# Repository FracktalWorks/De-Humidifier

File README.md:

# De-Humidifier

This is just a temporary file.

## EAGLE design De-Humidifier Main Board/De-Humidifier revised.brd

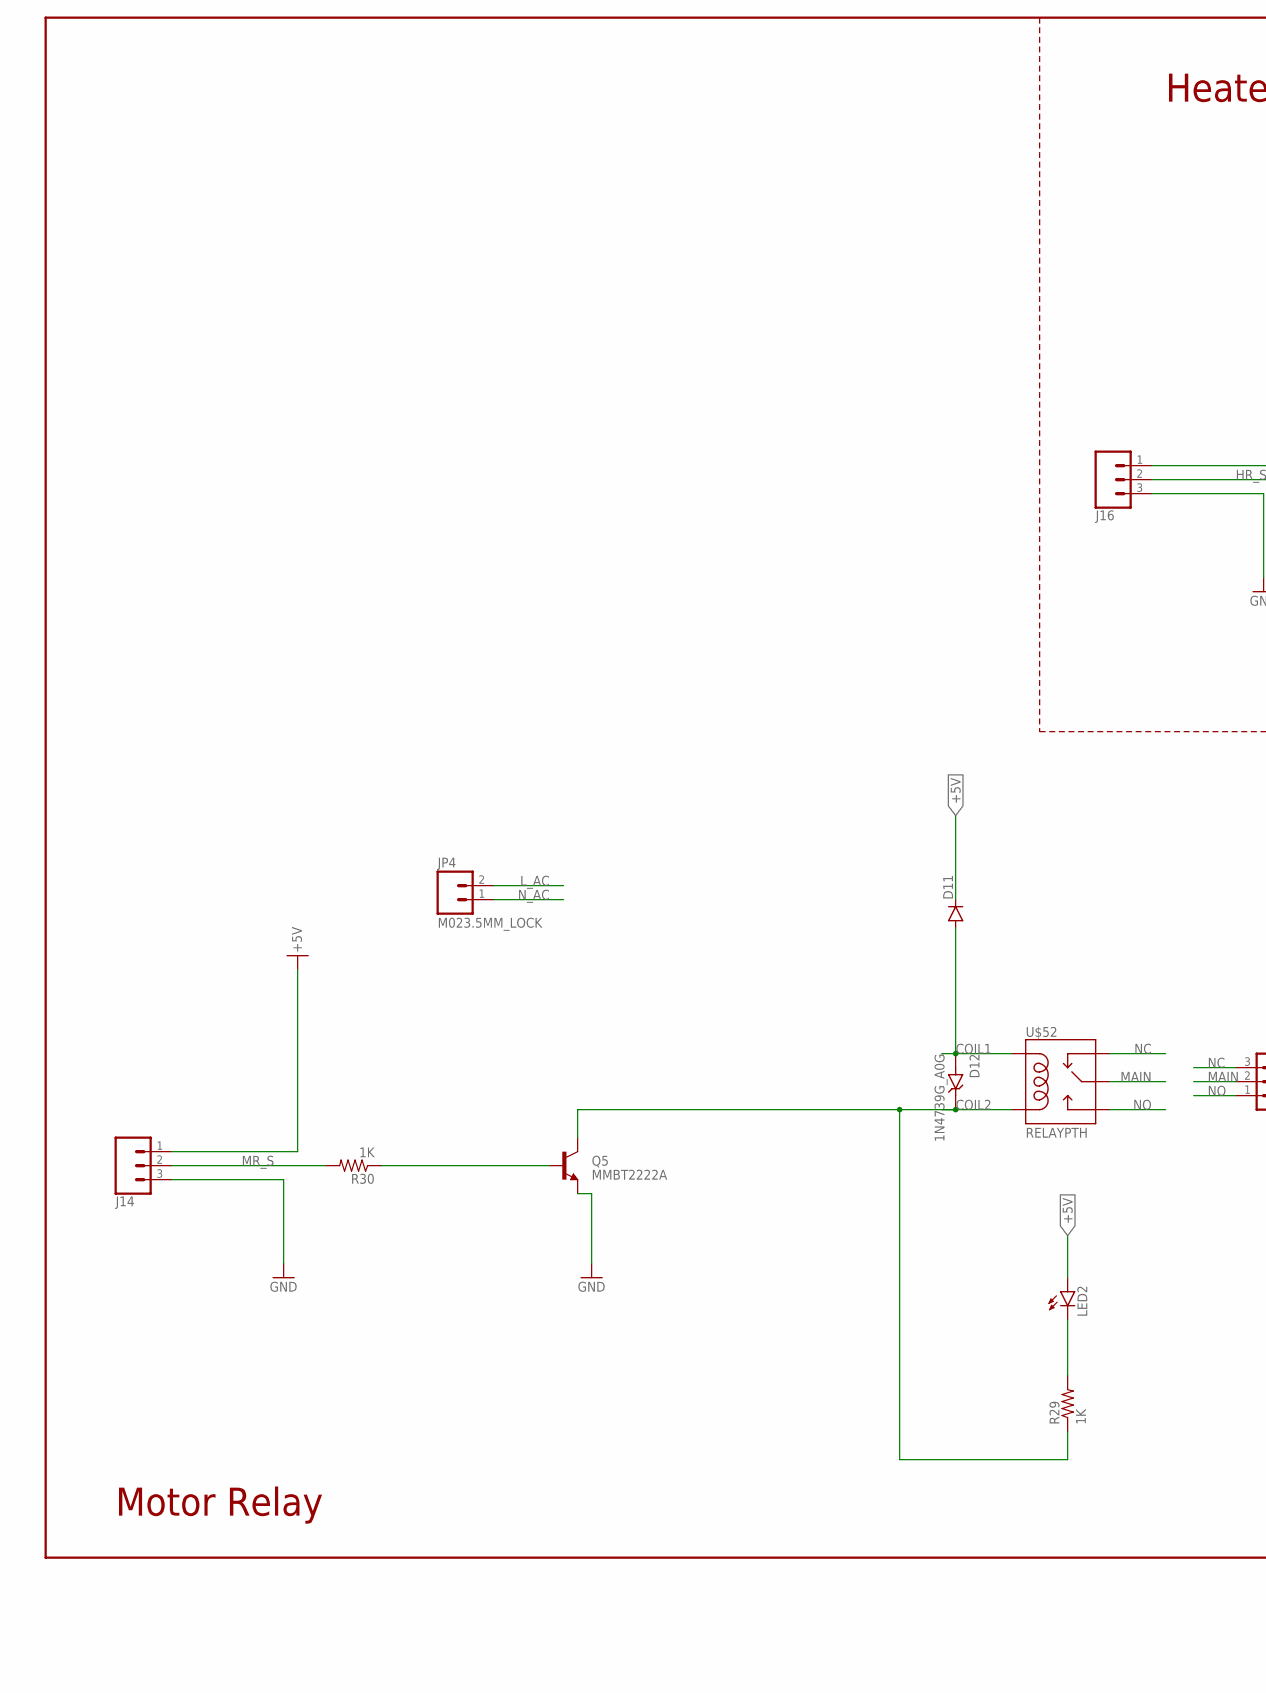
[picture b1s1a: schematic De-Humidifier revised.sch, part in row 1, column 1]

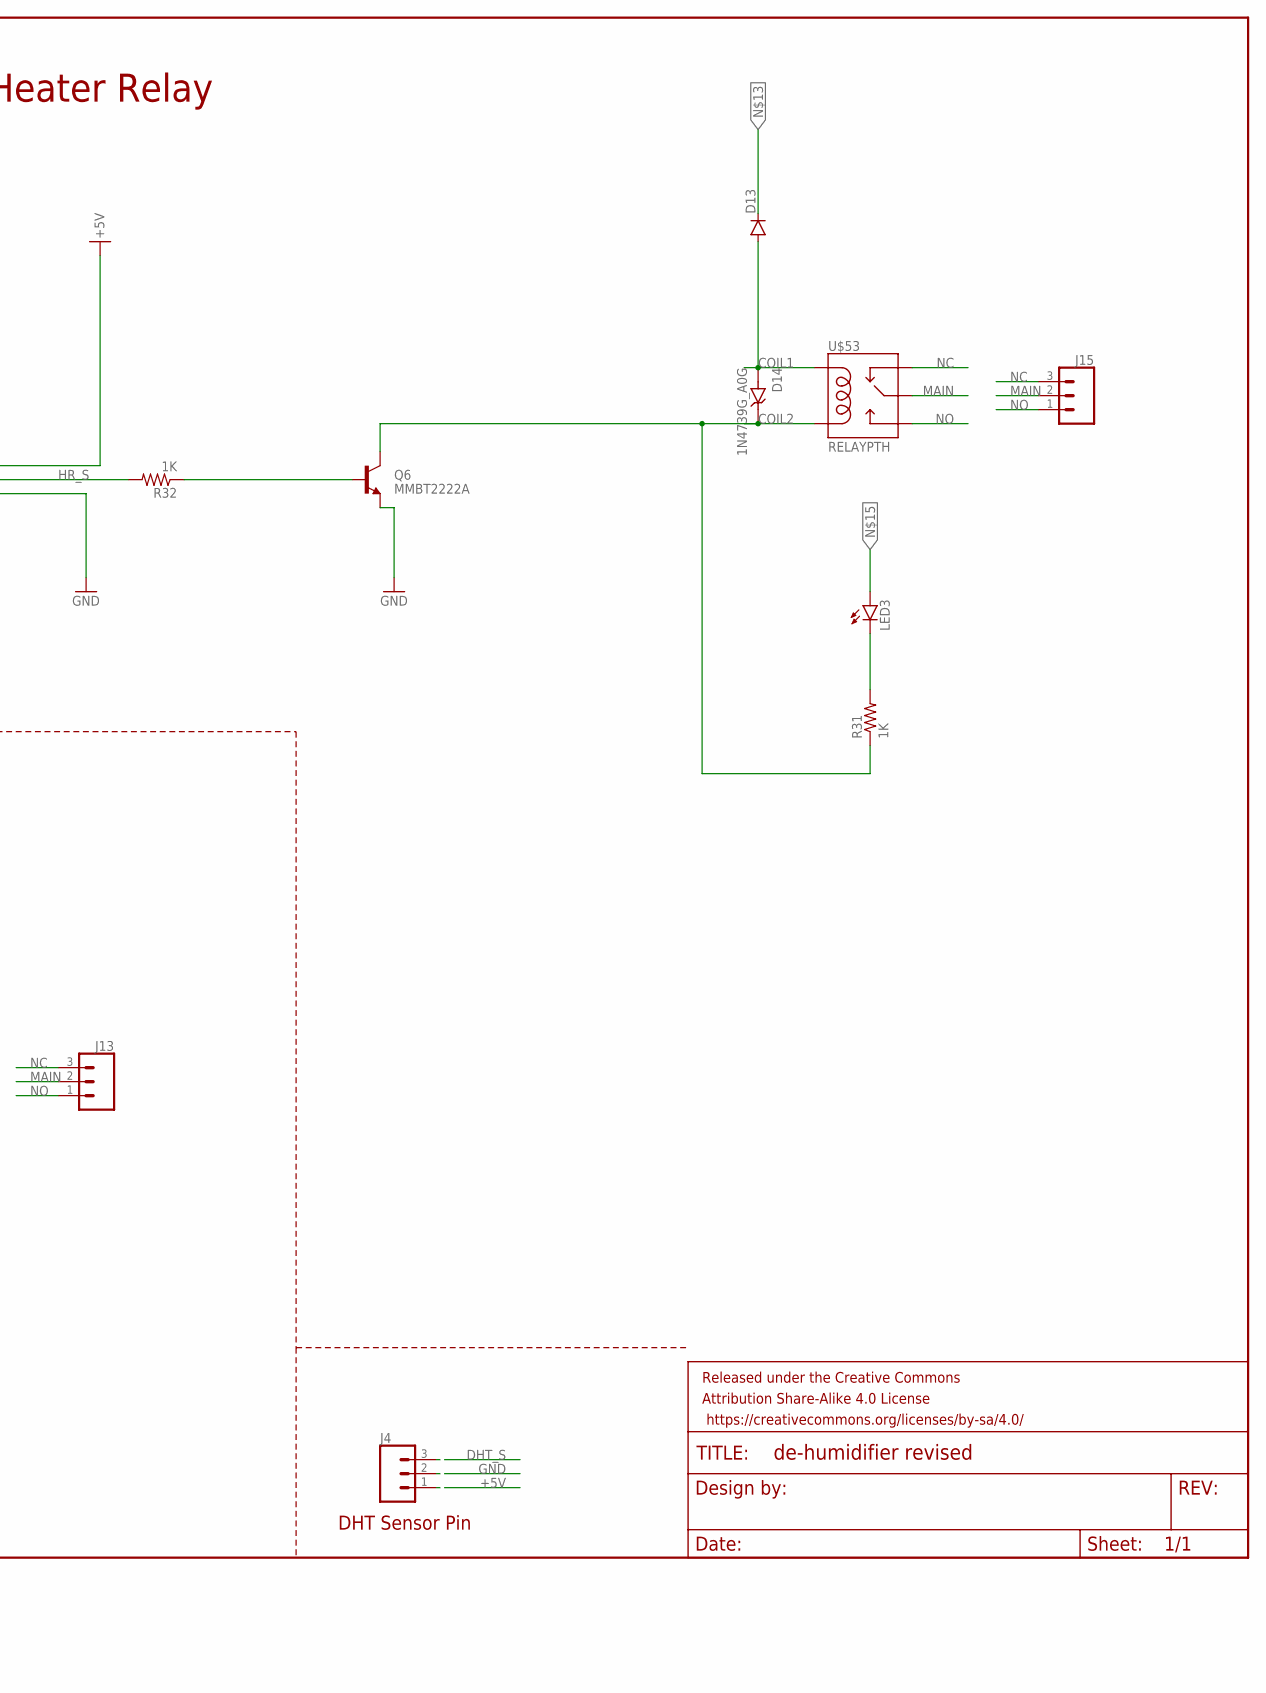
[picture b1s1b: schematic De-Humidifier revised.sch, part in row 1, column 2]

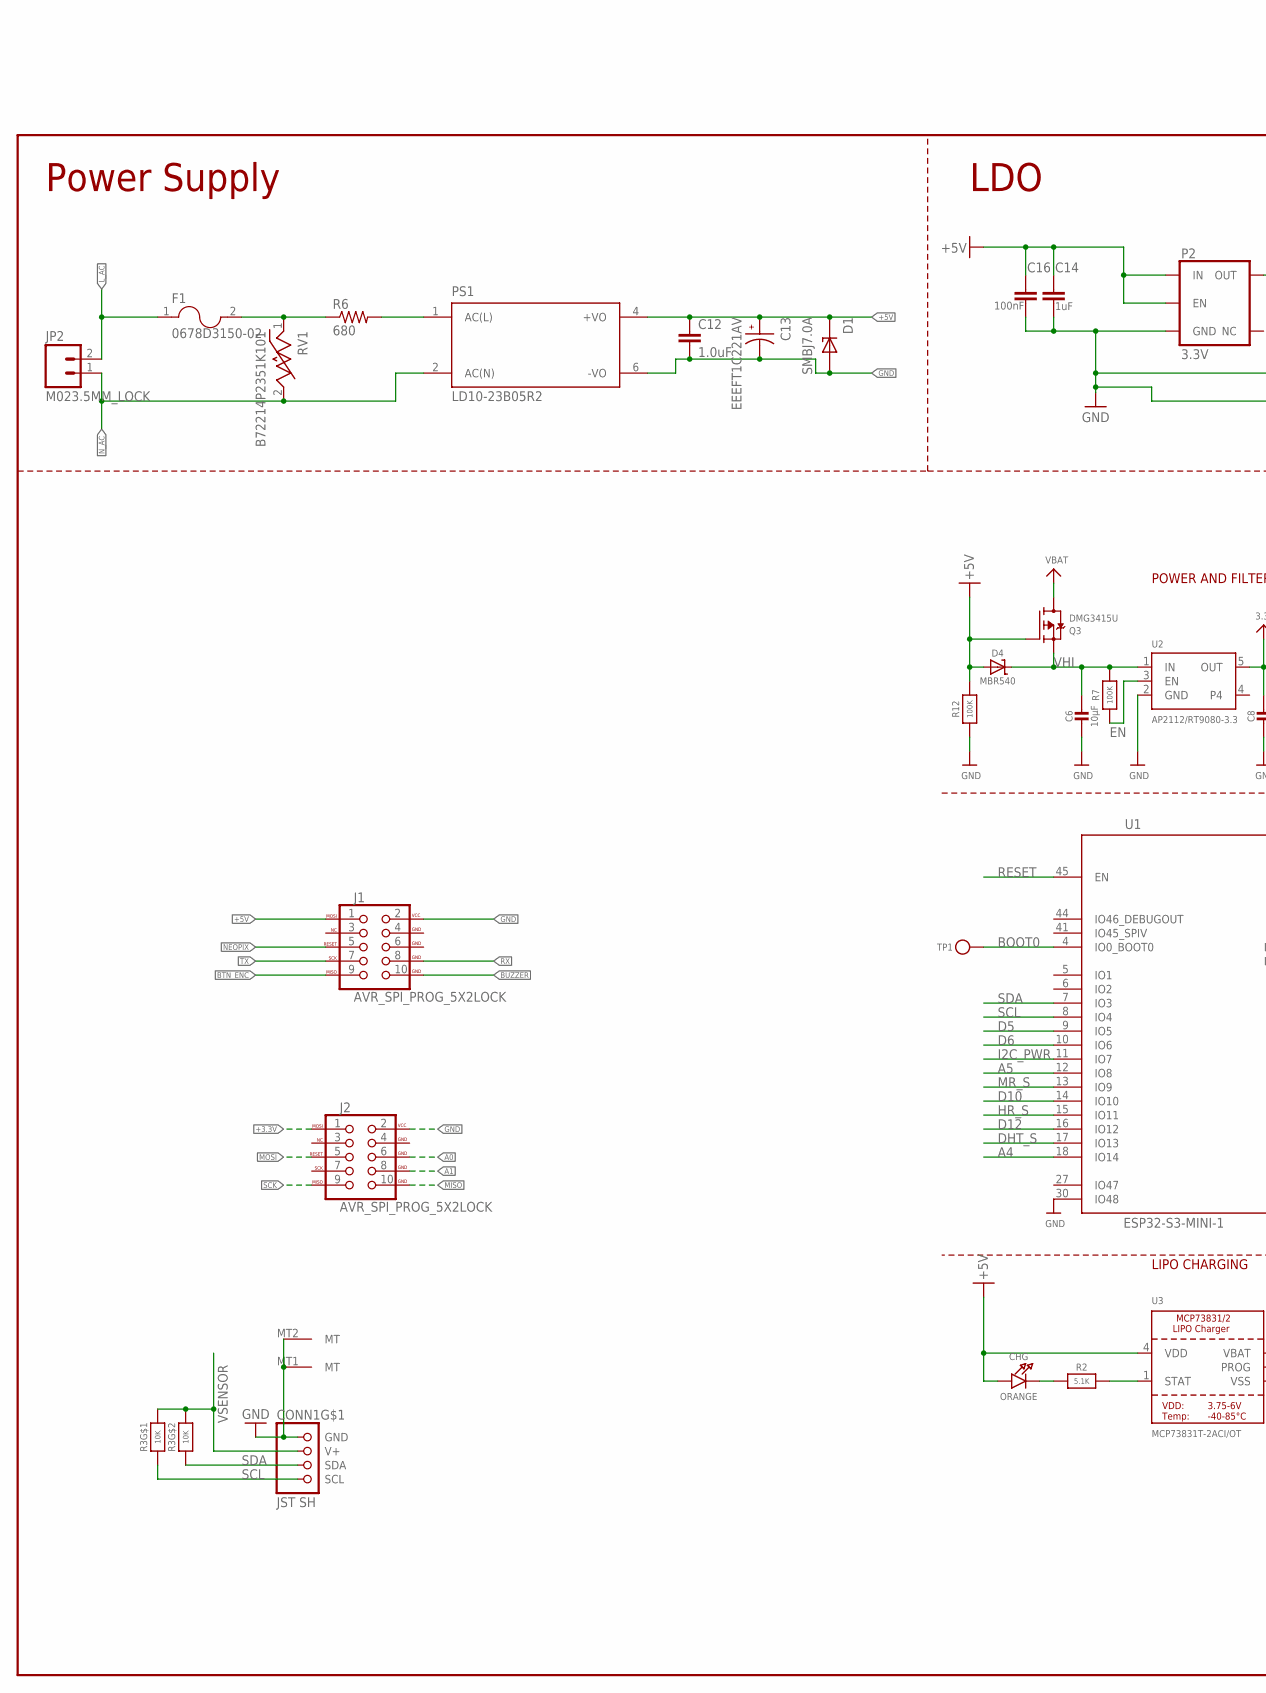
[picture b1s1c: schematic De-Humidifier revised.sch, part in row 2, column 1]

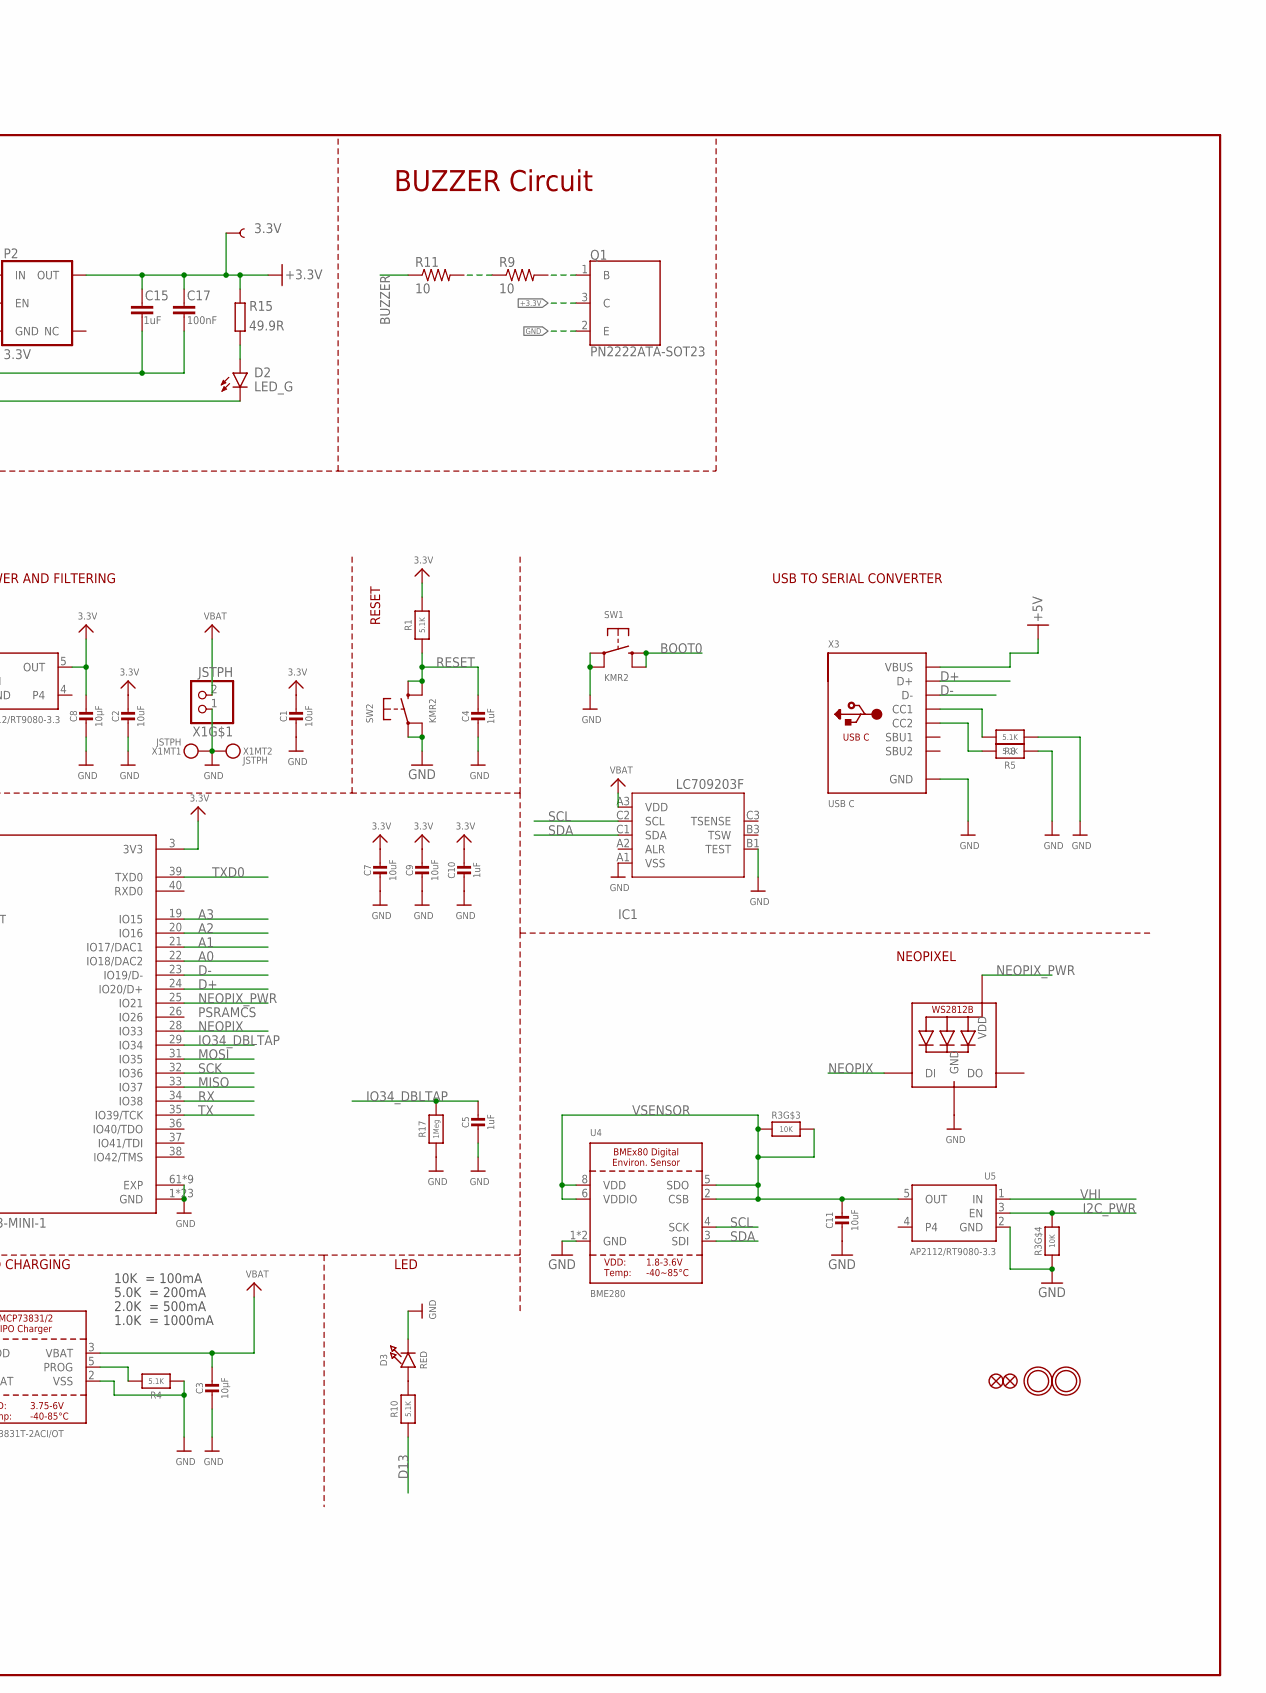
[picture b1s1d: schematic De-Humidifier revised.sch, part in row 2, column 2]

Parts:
3.3V: TEST-POINT3X4; PAD.03X.04
C1, C2, C7, C9: 10uF; 0805-NO
C3, C6, C8: 10µF; 0805-NO
C4, C5, C10: 1uF; 0603-NO
C11: 10uF; _0805MP
C12: 1.0uF; 0805
C13: EEEFT1C221AV; CAP_EEEFT1C221AV
C14, C15: 1uF; CAPC1005X60; LCSCPN# C52923
C16, C17: 100nF; CAPC1005X60; LCSCPN# C307331
CHG: ORANGE; CHIPLED_0603_NOOUTLINE
CONN1: JST SH; JST_SH4_RA
D1: SMBJ7.0A; DIOM4336X265N
D2: LED_G; LEDC1608X35N_FLAT-G; LCSCPN# C72043
D3: RED; CHIPLED_0603_NOOUTLINE
D4: MBR540; SOD-123
D11, D13: DIODEKIT; DIODE-1N4148-KIT
D12, D14: 1N4739G_A0G; DIOAD1036W73L450D282
F1: 0678D3150-02; FUSC9830X318N
FRAME2, FRAME3: FRAME-LEDGER; CREATIVE_COMMONS
IC1: LC709203F/MH; WLCSP9
J1, J2: AVR_SPI_PROG_5X2LOCK; 2X5-SHROUDED_LOCK
J4: CONN_03LONGPADS; 1X03_LONGPADS
J13, J14, J15, J16: CONN_03-SCREW-5MM; SCREWTERMINAL-5MM-3
JP2, JP4: M023.5MM_LOCK; SCREWTERMINAL-3.5MM-2_LOCK
LED1: WS2812B_SK6805_1515; SK6805_1515
LED2, LED3: LED-FKIT-1206; FKIT-LED-1206
P2: 3.3V; SOT23-5; LCSCPN# C51118
PS1: LD10-23B05R2; CONV_LD10-23B05R2
Q1: PN2222ATA-SOT23; SOT23-3
Q3: DMG3415U; SOT23-R
Q5, Q6: MMBT2222A; SOT23-3
R1, R2, R4, R5, R8, R10: 5.1K; 0603-NO
R3: 10K; RESPACK_4X0603
R6: 680; 0603-RES
R7, R12: 100K; 0603-NO
R9, R11: 10; 0603-RES
R15: 49.9R; RESC1005X40; LCSCPN# C25120
R17: 1Meg; 0603-NO
R29, R30, R31, R32: 1K; 0603-RES
RV1: B72214P2351K101; VAR_B72214P2351K101
SW1, SW2: KMR2; BTN_KMR2_4.6X2.8
TP1: TESTPOINTROUND1.5MMNO; TESTPOINT_ROUND_1.5MM_NO
U1: ESP32-S3-MINI-1; QFN60_ESP32-S2-MINI-1_EXP
U2, U5: AP2112/RT9080-3.3; SOT23-5
U3: MCP73831T-2ACI/OT; SOT23-5
U4: BME280
U$31, U$32: MOUNTINGHOLE2.5; MOUNTINGHOLE_2.5_PLATED
U$34, U$35: FIDUCIAL_1MM
U$52, U$53: RELAYPTH; RELAY-G5Q
X1: JSTPH; JSTPH2_BATT
X3: USB C; USB_C_CUSB31-CFM2AX-01-X

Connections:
3.3V: C1.1, C2.1, C7.1, C8.1, C9.1, C10.1, R1.2, U1.3 (3V3), U2.5 (OUT)
+3.3V: 3.3V.P$1, C15.1, C17.1, J2.1 (MOSI), P2.5 (OUT), Q1.3 (C), R15.2
+5V: C12.1, C13.1, C14.1, C16.1, CHG.A, D1.C, D4.A, D11.C, J1.1 (MOSI), J4.1, J14.1, J16.1, LED2.A, P2.1 (IN), P2.3 (EN), PS1.4 (+VO), Q3.1 (G), R12.2, U3.4 (VDD), X3.A4B9 (VBUS), X3.B4A9 (VBUS)
A0: J2.6 (GND), U1.22 (IO18/DAC2)
A1: J2.8 (GND), U1.21 (IO17/DAC1)
A2: U1.20 (IO16)
A3: U1.19 (IO15)
A4: U1.18 (IO14)
A5: U1.12 (IO8)
BOOT0: SW1.B (S), SW1.B' (S1), TP1.P$1, U1.4 (IO0_BOOT0)
BTN_ENC: J1.9 (MISO)
BUZZER: J1.10 (GND), R11.1
COIL1: D11.A, D12.A, D13.A, D14.A, U$52.5 (COIL1), U$53.5 (COIL1)
COIL2: D12.C (K), D14.C (K), Q5.3 (C), Q6.3 (C), R29.1, R31.1, U$52.1 (COIL2), U$53.1 (COIL2)
D5: U1.9 (IO5)
D6: U1.10 (IO6)
D10: U1.14 (IO10)
D12: U1.16 (IO12)
D13: R10.1
D+: U1.24 (IO20/D+), X3.A6 (D+), X3.B6 (D+)
D-: U1.23 (IO19/D-), X3.A7 (D-), X3.B7 (D-)
DHT_S: J4.3, U1.17 (IO13)
EN: R7.1, U2.3 (EN)
GND: C1.2, C2.2, C3.2, C4.2, C5.2, C6.2, C7.2, C8.2, C9.2, C10.2, C11.2, C12.2, C13.2, C14.2, C15.2, C16.2, C17.2, CONN1.1 (GND), CONN1.MT1 (MT), CONN1.MT2 (MT), D1.A, D2.C, D3.C, IC1.A1 (VSS), IC1.B1 (TEST), J1.2 (VCC), J1.4 (GND), J1.6 (GND), J2.2 (VCC), J2.4 (GND), J4.2, J14.3, J16.3, LED1.4 (GND), P2.2 (GND), PS1.6 (-VO), Q1.2 (E), Q5.2 (E), Q6.2 (E), R3.4 (1), R4.1, R5.1, R8.1, R12.1, R17.1, SW1.A, SW1.A' (P1), SW2.A, SW2.A' (P1), U1.1 (GND), U1.2 (GND), U1.30 (IO48), U1.42 (GND), U1.43 (GND), U1.46 (GND), U1.47 (GND), U1.48 (GND), U1.49 (GND), U1.50 (GND), U1.51 (GND), U1.52 (GND), U1.53 (GND), U1.54 (GND), U1.55 (GND), U1.56 (GND), U1.57 (GND), U1.58 (GND), U1.59 (GND), U1.60 (GND), U1.61 (EXP), U1.62 (GND), U1.63 (GND), U1.64 (GND), U1.65 (GND), U1.66 (EXP), U1.67 (EXP), U1.68 (EXP), U1.69 (EXP), U1.70 (EXP), U1.71 (EXP), U1.72 (EXP), U1.73 (EXP), U2.2 (GND), U3.2 (VSS), U4.1 (GND), U4.7 (GND), U5.2 (GND), X1.1, X1.NC1, X1.NC2, X3.A1B12 (GND), X3.B1A12 (GND)
HR_S: J16.2, R32.2, U1.15 (IO11)
I2C_PWR: R3.5 (2), U1.11 (IO7), U5.3 (EN)
IO34_DBLTAP: C5.1, R17.2, U1.29 (IO34)
L_AC: F1.1, JP2.2, JP4.2
MAIN: J13.2, J15.2, U$52.2 (MAIN), U$53.2 (MAIN)
MISO: J2.10 (GND), U1.33 (IO37)
MOSI: J2.5 (RESET), U1.31 (IO35)
MR_S: J14.2, R30.2, U1.13 (IO9)
unnamed: CHG.C, R2.1
unnamed: F1.2, R6.1, RV1.1
unnamed: R2.2, U3.1 (STAT)
unnamed: R4.2, U3.5 (PROG)
unnamed: D3.A, R10.2
unnamed: PS1.1 (AC(L)), R6.2
unnamed: Q1.1 (B), R9.2
unnamed: R8.2, X3.A5 (CC1)
unnamed: R5.2, X3.B5 (CC2)
unnamed: R9.1, R11.2
unnamed: D2.A, R15.1
unnamed: LED2.C, R29.2
unnamed: Q5.1 (B), R30.1
unnamed: LED3.C, R31.2
unnamed: Q6.1 (B), R32.1
NC: J13.3, J15.3, U$52.4 (NC), U$53.4 (NC)
NEOPIX: J1.5 (RESET), LED1.1 (DI), U1.28 (IO33)
NEOPIX_PWR: LED1.2 (VDD), U1.25 (IO21)
NO: J13.1, J15.1, U$52.3 (NO), U$53.3 (NO)
N_AC: JP2.1, JP4.1, PS1.2 (AC(N)), RV1.2
RESET: C4.1, R1.1, SW2.B (S), SW2.B' (S1), U1.45 (EN)
RX: J1.8 (GND), U1.34 (IO38)
SCK: J2.9 (MISO), U1.32 (IO36)
SCL: CONN1.4 (SCL), IC1.C2 (SCL), R3.1, U1.8 (IO4), U4.4 (SCK)
SDA: CONN1.3 (SDA), IC1.C1 (SDA), R3.2 (1), U1.7 (IO3), U4.3 (SDI)
TX: J1.7 (SCK), U1.35 (IO39/TCK)
TXD0: U1.39 (TXD0)
VBAT: C3.1, IC1.A3 (VDD), Q3.3 (D), U3.3 (VBAT), X1.2
VHI: C6.1, D4.C, Q3.2 (S), R7.2, U2.1 (IN), U5.1 (IN)
VSENSOR: C11.1, CONN1.2 (V+), R3.3 (1), R3.6 (2), R3.7 (2), R3.8 (2), U4.2 (CSB), U4.5 (SDO), U4.6 (VDDIO), U4.8 (VDD), U5.5 (OUT)

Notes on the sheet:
POWER AND FILTERING
RESET
10K = 100mA
5.0K = 200mA
2.0K = 500mA
1.0K = 1000mA
USB TO SERIAL CONVERTER
LIPO CHARGING
LED
PSRAMCS
NEOPIXEL
Power Supply
LDO
BUZZER Circuit
Motor Relay
Heater Relay
DHT Sensor Pin

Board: 2 copper layers, 85 parts (0 on the bottom side), 51 nets, no tracks yet.

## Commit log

2023-07-27 Added the prototype code for the de-humidifier project
2023-07-27 README.md
2023-11-28 Initial schematic design of the Main Board
2024-03-13 Updated the code as per ESP32 S3 Wroom 32 1 N16
2024-03-15 Created Production Folder, organized files for VS code/ platform.io compilation
2024-03-15 Optimized encoder and buzzer functionality
2024-04-11 Added Preheating Time Functionality
2024-05-15 updated the LCD display encoder pin definition

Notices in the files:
parts and their libraries:
microbuilder: This work is placed in the public domain, and may be freely used for commercial and non-commercial work with the following conditions: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
SparkFun-Aesthetics: Licensing: Creative Commons ShareAlike 4.0 International - https://creativecommons.org/licenses/by-sa/4.0
